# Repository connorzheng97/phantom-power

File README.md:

# What is this

This is a 3-AA-battery powered phantom power supply. It was intended for use with wireless microphone beltpacks to provide high quality 48V phantom power to large condenser microphones and enable them to be used wirelessly, or as a standalone unit. It's also suitable for DI boxes, small condenser microphones and anything requiring phantom power.

This is a complete design with schematic, PCB and enclosure. Files are production-ready, with BOM. Design of this project begun in 2019 and final test was done on December of 2021. Batch production was planned but hasn't been carried out, as newer wireless microphone beltpacks has begun to incorporate built-in phantom power circuits (although usually not at full 48V), and COVID has had a major impact on touring industry.

# The Specs
- Power Source: 3x AA Batteries, alkaline is recommended. Ni-Mh rechargeable can also be used.
- Battery Run Time: depends on load and actual battery capacity, 5 to 72 hours typically
- Battery Indicator: yes, two LEDs for normal and low battery
- Power Output: IEC 61938, 48VDC ±2V
- Phantom Resistor: 6.81K
- Current: up to about 14mA at short-circuit
- Noise: < 100uVpp
- EMI: not tested

# The Design
## Overall Design

A simple power supply box with XLR-in (connects to device requiring phantom power), XLR-out (no DC bias, connect to audio input of next stage), a power switch and a battery voltage indicator. The switch is partly recessed to avoid accidental operation. The colors of the battery indicator are ice-blue and orange, which are color-blind friendly. On the side of the box are 2 ears where you can thread in a hook-and-loop nylon cable tie to form a loop and strap the box to wireless beltpack and microphone stand or other fixation points.

## Schematic and PCB
Schematic and PCB were done with KiCAD 5. A [PDF version of the schematic](./docs/phantom_v1.pdf) is available for view under the `docs` folder.

Circuit consists of a simple boost converter with added 3-stage diode voltage multiplier, a high voltage LDO, and a 2-stage Darlington capacitance multiplier for lowest noise possible. Protection circuitry and battery voltage indication were also added. A P-MOS blocks reverse battery, followed by a PPTC resettable fuse and transient suppression.

PCB is a normal 1.6mm 2-layer PCB.

## Mechanical Design
Enclosure design was done with Solidworks 2018. STEP and STL files are also provided in the `mech` folder. The design is mostly complete, and should be injection-molding ready, with no draft angle in design file. 

The PCB is held down to the base part by boss from top part, which are held down to base part by self-tapping screws. The holes in the bosses are through, which are also used to mount the battery holder. The front panel is held in place by groves on both large parts. The battery holder is an off-the-shelf one which can be bought on Taobao or AliExpress. XLR connectors are fixed to front panel with self-tapping screws.

# Make Your Own
You can fabricate the PCB and have it partly assembled by a PCB fab such as PCBWay(JDB PCB) or JLC-PCB. Solder only the common SMT parts at the fab, which I found to be the most cost-saving. A gerber file set is included in the `output` folder in the hardware design files. Other parts can be sourced from LCSC or another distributor. Hand soldering is mostly easy except the VSSOP LDO may be a little bit annoying. Alternative part number may be found in schematic.

Enclosure can be 3D-printed either at home or by a professional service. For FDM 3D-printing, remove small details that are not printable. Print top part upside down with support.

A BOM for assembling can be found under the `docs` folder. A interactive BOM for the pcb can be found in the `ibom` folder under the `docs` folder.

## Assembling
1. Push light pipe onto PCB
2. Mount front panel to XLR connectors with 4 ST2.9x8 screws
3. Solder XH2.54 pigtail to battery holder
4. Mount battery holder onto top part of box with 4 ST3x10 screws
5. Place PCB and front panel into base part
6. Plug in battery XH2.54 plug
7. Screw top and base part together with 4 ST3x12 screws
8. Thread in hook-and-loop nylon cable tie

# Use of This Repo
This repo is licensed under CERN-OHL-W v2. In addition, consider buying me a drink if you like this design. You can credit back to my personal website as well if you wish.

This source describes Open Hardware and is licensed under the CERN-OHLW v2 

You may redistribute and modify this documentation and make products using it under the terms of the CERN-OHL-W v2 (https:/cern.ch/cern-ohl). 

This documentation is distributed WITHOUT ANY EXPRESS OR IMPLIED WARRANTY, INCLUDING OF MERCHANTABILITY, SATISFACTORY QUALITY AND FITNESS FOR A PARTICULAR PURPOSE. 
Please see the CERN-OHL-W v2 for applicable conditions. 

As per CERN-OHL-W v2 section 4.1, should You produce hardware based on these sources, You must maintain the Source Location visible on the external case of the phantom power supply or other product you make using this documentation.

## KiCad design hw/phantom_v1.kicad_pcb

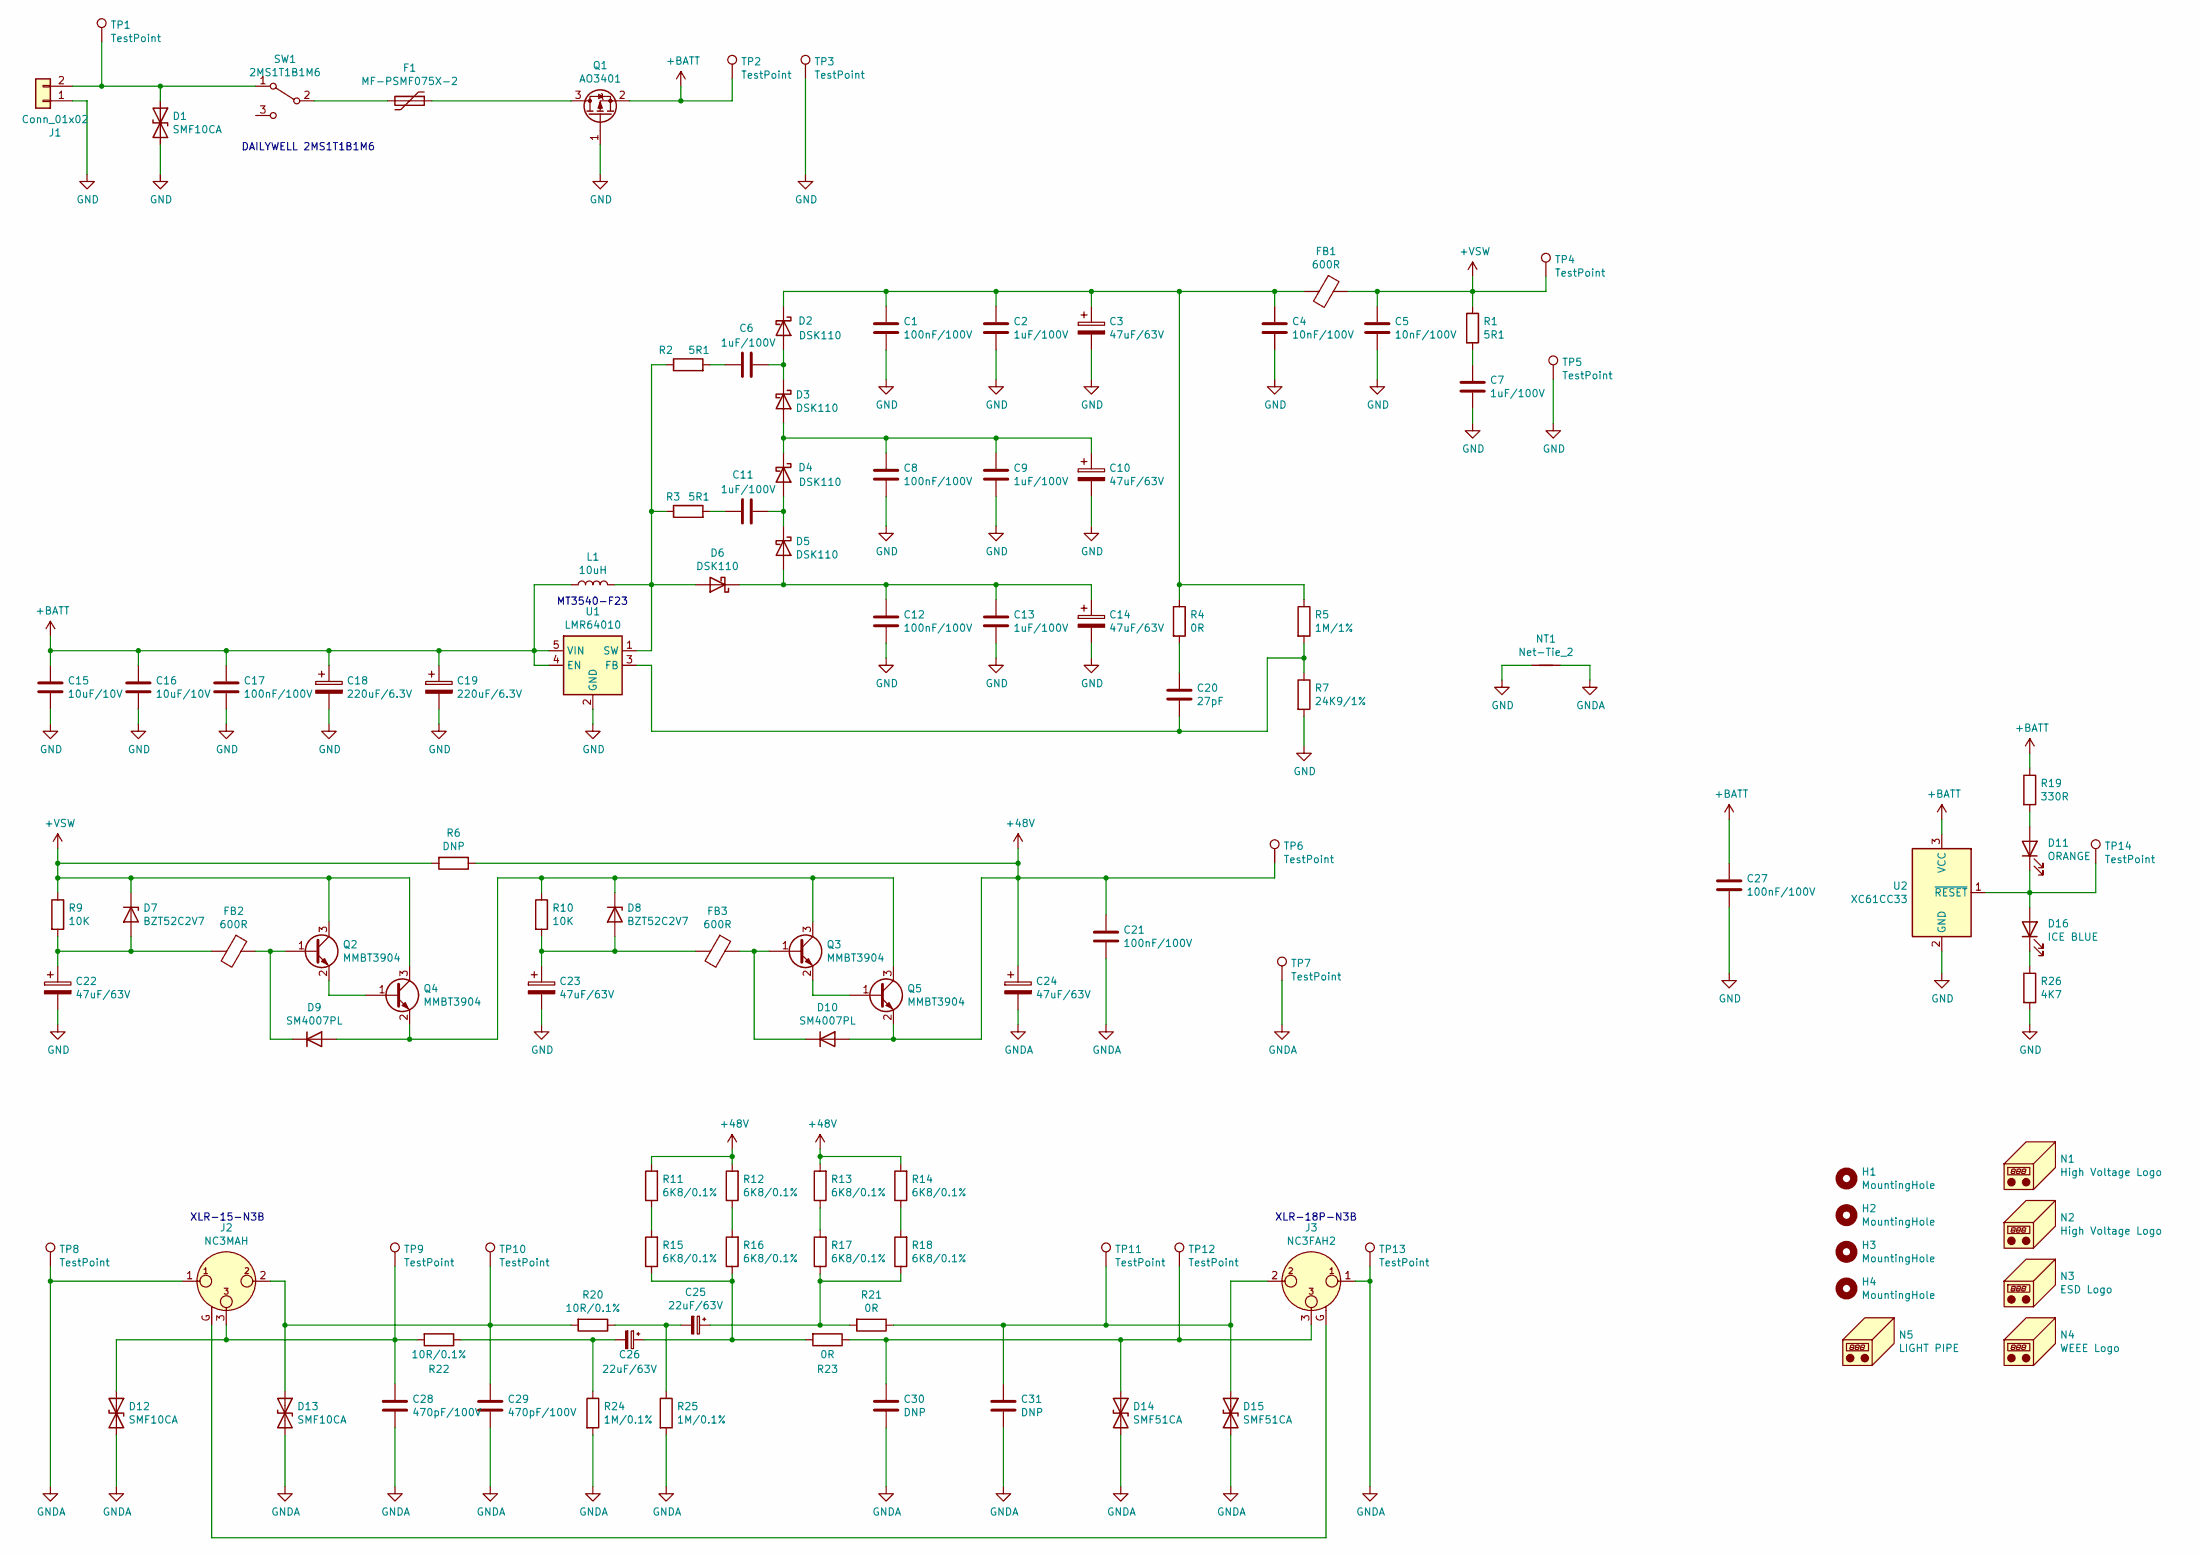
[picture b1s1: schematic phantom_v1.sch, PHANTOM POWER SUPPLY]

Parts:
C1, C8, C12, C17, C21, C27: 100nF/100V; C_0805_2012Metric
C2, C6, C7, C9, C11, C13: 1uF/100V; C_1206_3216Metric
C3, C10, C14, C22, C23, C24: 47uF/63V; CP_Radial_D6.3mm_P2.50mm
C4, C5: 10nF/100V; C_0805_2012Metric
C15, C16: 10uF/10V; C_0805_2012Metric
C18, C19: 220uF/6.3V; CP_Radial_D5.0mm_P2.00mm
C20: 27pF; C_0603_1608Metric
C25, C26: 22uF/63V; CP_Radial_D6.3mm_P2.50mm
C28, C29: 470pF/100V; C_0603_1608Metric
C30, C31: DNP; C_0603_1608Metric
D1, D12, D13: SMF10CA; D_SOD-123
D2, D3, D4, D5, D6: DSK110; D_SOD-123
D7, D8: BZT52C2V7; D_SOD-123
D9, D10: SM4007PL; D_SOD-123
D11: ORANGE; LED_0603_1608Metric
D14, D15: SMF51CA; D_SOD-123
D16: ICE BLUE; LED_0603_1608Metric
F1: MF-PSMF075X-2; Fuse_0805_2012Metric
FB1, FB2, FB3: 600R; L_0603_1608Metric
H1, H2, H3, H4: MountingHole; MountingHole_3.2mm_M3
J1: Conn_01x02; JST_XH_B2B-XH-A_1x02_P2.50mm_Vertical
J2: NC3MAH; Jack_XLR_Neutrik_NC3MAH_Horizontal
J3: NC3FAH2; Jack_XLR_Neutrik_NC3FAH2_Horizontal
L1: 10uH; PowerInductor_SWPA40XX
N1, N2: High Voltage Logo; LOGO-Warning-High_Voltage-Silk
N3: ESD Logo; ESD-Logo_8.9x8mm_SilkScreen
N4: WEEE Logo; WEEE-Logo_5.6x8mm_SilkScreen
N5: LIGHT PIPE; MECH-Light_pipe_6.35mm
NT1: Net-Tie_2; NetTie-2_SMD_Pad0.5mm
Q1: AO3401; SOT-23
Q2, Q3, Q4, Q5: MMBT3904; SOT-23
R1, R2, R3: 5R1; R_0603_1608Metric
R4, R21, R23: 0R; R_0603_1608Metric
R5: 1M/1%; R_0603_1608Metric
R6: DNP; R_0603_1608Metric
R7: 24K9/1%; R_0603_1608Metric
R9, R10: 10K; R_0603_1608Metric
R11, R12, R13, R14, R15, R16, R17, R18: 6K8/0.1%; R_1206_3216Metric
R19: 330R; R_0603_1608Metric
R20, R22: 10R/0.1%; R_0603_1608Metric
R24, R25: 1M/0.1%; R_0603_1608Metric
R26: 4K7; R_0603_1608Metric
SW1: 2MS1T1B1M6; Switch-2MS1T2B2M6-SPDT-ONON-THT
TP1, TP2, TP3, TP4, TP5, TP6, TP7, TP8, TP9, TP10, TP11, TP12, TP13, TP14: TestPoint; TestPoint_Pad_D1.5mm
U1: LMR64010; SOT-23-5
U2: XC61CC33; SOT-23

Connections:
+48V: C21.1, C24.1, D10.2 (A), Q5.2 (E), R6.1, R11.2, R12.2, R13.2, R14.2, TP6.1
+BATT: C15.1, C16.1, C17.1, C18.1, C19.1, C27.1, L1.1, Q1.2 (S), R19.1, TP2.1, U1.4 (EN), U1.5 (VIN), U2.3 (VCC)
+VSW: C5.1, D7.1 (K), FB1.1, Q2.3 (C), Q4.3 (C), R1.1, R6.2, R9.1, TP4.1
GND: C1.2, C2.2, C3.2, C4.2, C5.2, C7.2, C8.2, C9.2, C10.2, C12.2, C13.2, C14.2, C15.2, C16.2, C17.2, C18.2, C19.2, C22.2, C23.2, C27.2, D1.2 (A2), J1.1, NT1.1, Q1.1 (G), R7.2, R26.2, TP3.1, TP5.1, U1.2 (GND), U2.2 (GND)
GNDA: C21.2, C24.2, C28.2, C29.2, C30.2, C31.2, D12.2 (A2), D13.2 (A2), D14.2 (A2), D15.2 (A2), J2.1, J3.1, NT1.2, R24.2, R25.2, TP7.1, TP8.1, TP13.1
unnamed: C1.1, C2.1, C3.1, C4.1, D2.1 (K), FB1.2, R4.1, R5.1
unnamed: C6.1, R2.2
unnamed: C6.2, D2.2 (A), D3.1 (K)
unnamed: C7.1, R1.2
unnamed: C8.1, C9.1, C10.1, D3.2 (A), D4.1 (K)
unnamed: C11.1, R3.2
unnamed: C11.2, D4.2 (A), D5.1 (K)
unnamed: C12.1, C13.1, C14.1, D5.2 (A), D6.1 (K)
unnamed: C20.1, R4.2
unnamed: C20.2, R5.2, R7.1, U1.3 (FB)
unnamed: C22.1, D7.2 (A), FB2.2, R9.2
unnamed: C23.1, D8.2 (A), FB3.2, R10.2
unnamed: C25.1, R17.1, R18.1, R21.2
unnamed: C25.2, R20.1, R25.1
unnamed: C26.1, R15.1, R16.1, R23.2
unnamed: C26.2, R22.1, R24.1
unnamed: C28.1, D12.1 (A1), J2.3, R22.2, TP9.1
unnamed: C29.1, D13.1 (A1), J2.2, R20.2, TP10.1
unnamed: C30.1, D14.1 (A1), J3.3, R23.1, TP12.1
unnamed: C31.1, D15.1 (A1), J3.2, R21.1, TP11.1
unnamed: D1.1 (A1), J1.2, SW1.1 (A), TP1.1
unnamed: D6.2 (A), L1.2, R2.1, R3.1, U1.1 (SW)
unnamed: D8.1 (K), D9.2 (A), Q3.3 (C), Q4.2 (E), Q5.3 (C), R10.1
unnamed: D9.1 (K), FB2.1, Q2.1 (B)
unnamed: D10.1 (K), FB3.1, Q3.1 (B)
unnamed: D11.1 (K), D16.2 (A), TP14.1, U2.1 (~RESET)
unnamed: D11.2 (A), R19.2
unnamed: D16.1 (K), R26.1
unnamed: F1.1, Q1.3 (D)
unnamed: F1.2, SW1.2 (B)
unnamed: J2.G, J3.G
unnamed: Q2.2 (E), Q4.1 (B)
unnamed: Q3.2 (E), Q5.1 (B)
unnamed: R11.1, R15.2
unnamed: R12.1, R16.2
unnamed: R13.1, R17.2
unnamed: R14.1, R18.2

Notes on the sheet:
MT3540-F23
XLR-18P-N3B
XLR-15-N3B
DAILYWELL 2MS1T1B1M6

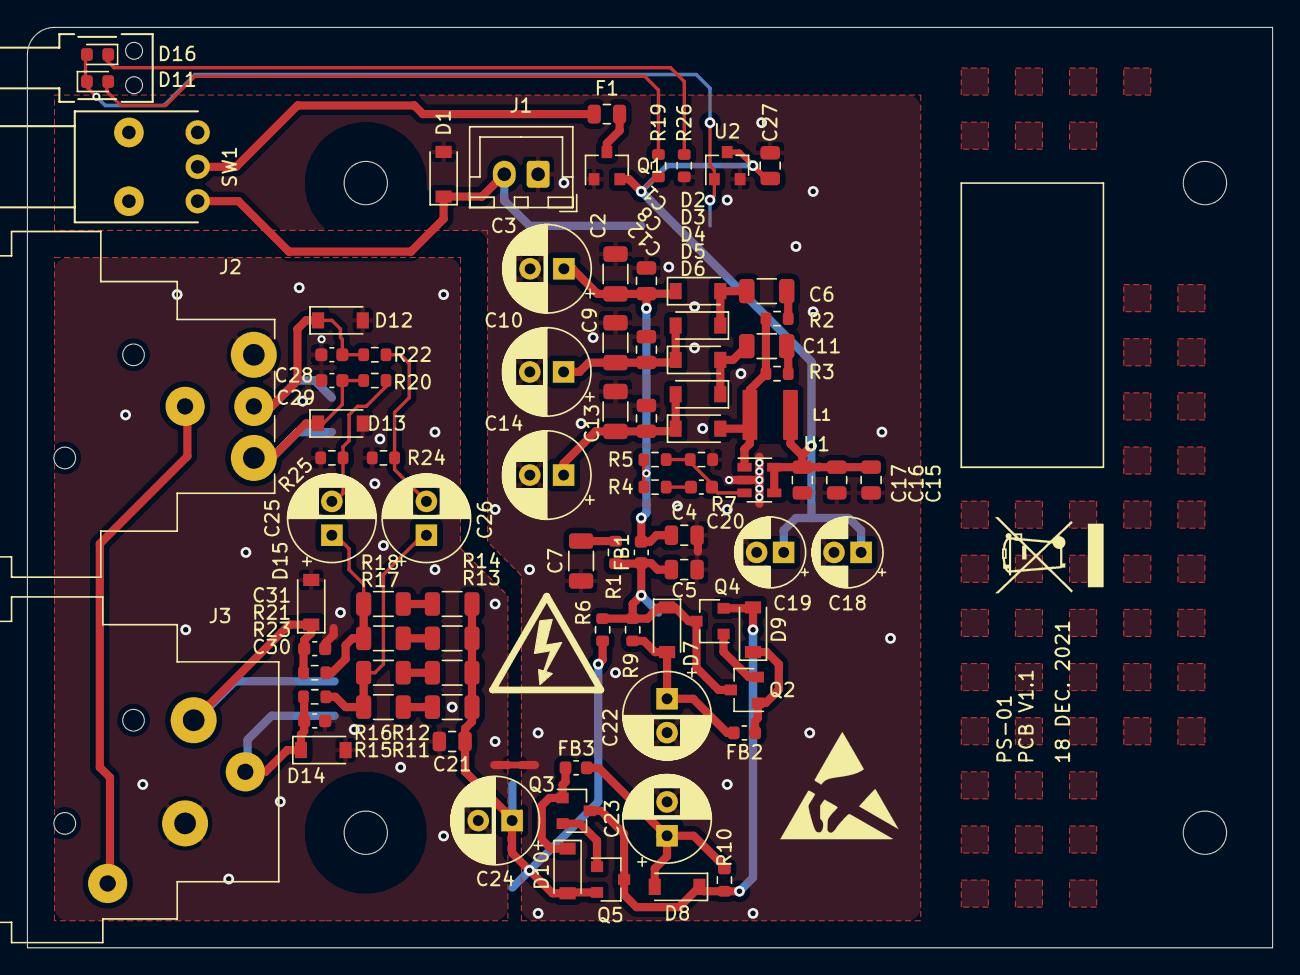
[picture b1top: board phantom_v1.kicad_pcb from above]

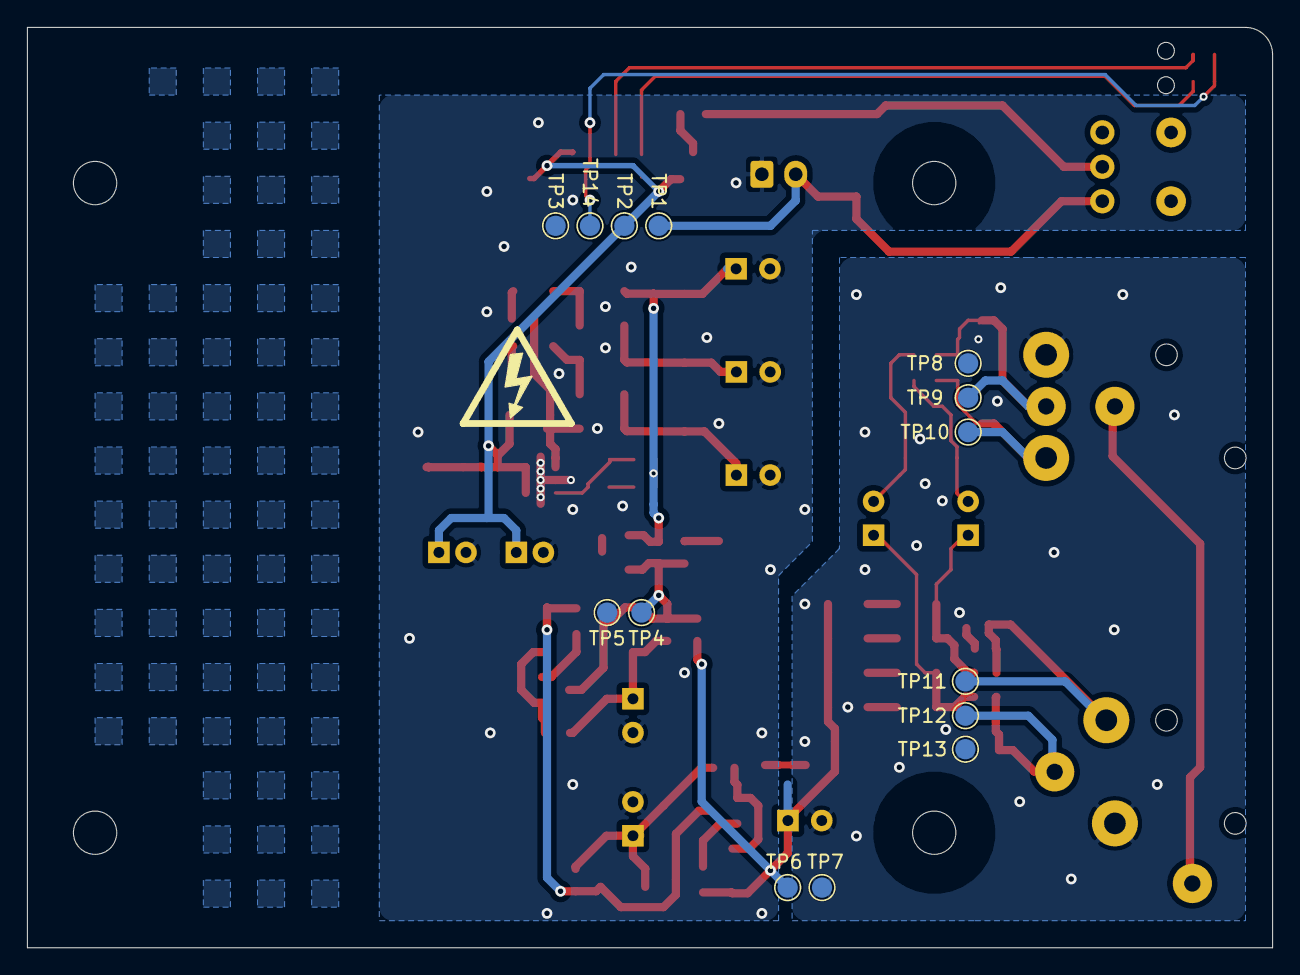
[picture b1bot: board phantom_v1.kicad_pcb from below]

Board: 2 copper layers, 92.0 x 68.0 mm, 112 parts (15 on the bottom side), 42 nets.

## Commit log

2022-07-20 Revert "Initial commit"
    This reverts commit c2769106053510e1000331ec69c7da4c13d6a57c.
